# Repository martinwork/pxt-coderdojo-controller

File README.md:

# pxt-coderdojo-controller
This is an open-source, low-cost, do-it-yourself game controller for the micro:bit. You cannot purchase a finished product. Instead, you'll need to gather all the components and assemble it yourself or with your class.  
[Read more in the hardware section for a detailed building guide](https://github.com/jimd80/pxt-coderdojo-controller/tree/main/hardware)

## Features
* 8 buttons: Up, Down, Left, Right, X, Y, A, B
* 2x AAA batteries, On/Off switch, and LED indicator
* Built-in speaker and customizable red LED
* Micro USB cable storage compartment
* Protection against short circuits and incorrect I/O usage
* Compatible with micro:bit v1.x and v2.x
* Over 100 hours of battery life

## Usage
Creating software for this controller can be done with [Microsoft MakeCode for micro:bit](https://makecode.microbit.org/)
* Create a new project and give it a name of your choice
* Click on Extensions in the block menu
* Search for coderDojo-controller and click on the thumbnail

After adding the extension, you'll find the specific blocks for this controller under ``Dojo Controller``

The blocks work the same as the standard micro:bit A and B buttons and can be used in 2 ways:  

* An event driven approach: use the ``on button pressed`` block. The code inside gets executed when a button is pressed/clicked. The behaviour can be changed to execute the code if the button is released instead.

```blocks
coderDojoController.onButtonPress(CoderDojoButtonID.X, CoderDojoButtonEvent.Pressed, function () {
    coderDojoController.setRedLed(CoderDojoLedState.On)
})
```

```blocks
coderDojoController.onButtonPress(CoderDojoButtonID.X, CoderDojoButtonEvent.Released, function () {
    coderDojoController.setRedLed(CoderDojoLedState.Off)
})
```

* Alternatively, a loop driven approach can be used with a standard ``if`` block combined with the ``button is pressed`` function. The code inside the ``if`` block will be executed multiple times, as long as the button is being pressed.

```blocks
basic.forever(function () {
    if (coderDojoController.buttonIsPressed(CoderDojoButton.X, CoderDojoButtonState.Pressed)) {
        coderDojoController.setRedLed(CoderDojoLedState.On)
    } else {
        coderDojoController.setRedLed(CoderDojoLedState.Off)
    }
})
```

Note that the A and B buttons on the micro:bit have the same function as the A and B buttons on the controller. You can use the extension without the controller hardware and have the extra buttons available when plugged into the controller.

## Build
cd into project folder  
npm install pxt  
pxt target microbit  
pxt gendocs --locs  
if needed: update translations in _locales/  
pxt build  

## Supported targets

* for PXT/microbit
(The metadata above is needed for package search.)

## License

MIT  

```package
coderdojo-controller=github:jimd80/pxt-coderdojo-controller
```

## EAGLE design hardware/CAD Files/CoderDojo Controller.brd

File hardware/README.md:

## Hardware building guide
The (empty) PCB can be easily manufactured by any PCB company, for example JLCPCB which is known as the cheapest. The cable holder at the back can be 3D printed with any 3D printer, for example the affordable Creality Ender V2 or V3.

Other parts can be ordered at various electronics suppliers such as LCSC, Aliexpress, Digikey, Farnell, ... The most difficult part to source will be the Micro:bit EDGE Connector. This needs to be the horizontal SMD type. Start finding this connector first before deciding to build this project.

Soldering can be done with (Lead free) soldering paste and a reflow oven, or if you are a bit handy it can also be done with a classical soldering iron, lead-free soldering wire and some flux. In that case it will be handy to have something to keep the parts in place while soldering, such as a screwdriver.

## Tools needed

You'll needs some tools and skills to build this project.
- A soldering iron and lead-free soldering wire
- Optionally, a reflow oven OR a hot air gun. Using this option you'll also need lead-free solder paste, such as Chipquik TS391SNL
- Recommended: Flux, such as Chipquik SMD291NL
- Cutting plier

## Step 1: Ordering the parts
Check out the [Bill of materials](https://github.com/jimd80/pxt-coderdojo-controller/blob/main/hardware/Bom.ods?raw=true). Parts can be ordered at various suppliers.

Part number      |Reference	            |Description                      |Qty|Price|Order link example|
:----------------|:---------------------|:--------------------------------|--:|----:|:-----------------|
R1,2,3,4,8,9     |Res 1K SMD0805        |Resistor 1K / 1% / 0,1W / 0805   |  6|€0.06|[LCSC](https://www.lcsc.com/product-detail/Chip-Resistor-Surface-Mount_YAGEO-RC0805FR-071KL_C95781.html)|
R5               |Res 100R SMD0805      |Resistor 100R / 1% / 0,1W / 0805 |  1|€0.01|[LCSC](https://www.lcsc.com/product-detail/Chip-Resistor-Surface-Mount_YAGEO-RC0805FR-07100RL_C105577.html)|
R6,7             |Res 470R SMD0805      |Resistor 470R / 1% / 0,1W / 0805 |  2|€0.02|[LCSC](https://www.lcsc.com/product-detail/Chip-Resistor-Surface-Mount_YAGEO-RC0805FR-07470RL_C114564.html)|
C1,2 (Optional)  |Cap 4u7 16v SMD1206   |Capacitor 4u7 / 16V / SMD 1206   |  2|€0.04|[LCSC](https://www.lcsc.com/product-detail/Multilayer-Ceramic-Capacitors-MLCC-SMD-SMT_Samsung-Electro-Mechanics-CL31B475KBHNNNE_C51205.html)|
LD1              |LED Red SMD0805       |Led Red SMD 0805                 |  1|€0.02|[LCSC](https://www.lcsc.com/product-detail/LED-Indication-Discrete_XINGLIGHT-XL-2012SURC_C965812.html)|
LD2              |LED Green SMD0805     |Led Green SMD 0805               |  1|€0.02|[LCSC](https://www.lcsc.com/product-detail/LED-Indication-Discrete_XINGLIGHT-XL-2012UGC_C965815.html)|
F1               |Polyfuse 500mA SMD1812|Polyfuse 30V / 500mA / SMD 1812  |  1|€0.08|[Aliexpress](https://www.aliexpress.com/item/1005006431435556.html)|
BUZ1             |9042 16R Passive      |Passive piezo sounder 3-5v       |  1|€0.19|[Aliexpress](https://www.aliexpress.com/item/1005006230919996.html)|
SW1,2,3,4,6,7,8,9|Pushbutton 6x6x5mm    |Pushbutton (on)-off 6x6x5mm      |  8|€0.05|[Aliexpress](https://www.aliexpress.com/item/1005001897291190.html)|
SW5              |Switch SS-12F23       |Slider switch 50v/0,5A spdt      |  1|€0.08|[Aliexpress](https://www.aliexpress.com/item/1005004508647910.html)|
BATT1            |2XAAA Battery Box     |Battery holder 2x AAA center hole|  1|€0.36|[Aliexpress](https://www.aliexpress.com/item/1005006274732583.html)|
J1               |Edge connector hor SMD|Micro:bit edge connector SMD/hor |  1|€0.85|[Aliexpress](https://www.aliexpress.com/item/1005006206948907.html)|
Other            |SMTSO M3 1ET          |SMD M3 Nut Length 1,5 + 1mm      |  1|€0.22|[Aliexpress](https://www.aliexpress.com/item/1005007226371037.html)|
Other            |Screw M3x6            |Screw M3x6 countersunk           |  1|€0.04|[Aliexpress](https://www.aliexpress.com/item/4000983507018.html)|

- C1 and C2 are not really required but can avoid software resets when shaking the controller heavilly
- BUZ1 is not required if using a micro:bit v2 or if sound is not preferred
- The most difficult part to find will be the EDGE connector, this needs to be the horizontal SMD version, and needs to look exactely like this

## Step 2: Ordering the PCB
The PCB (without components) needs to be manufactored by a company. These are the instructions for JLCPCB.
- Go to (https://jlcpcb.com)
- Choose "Add gerber file" and upload [CoderDojo Controller JLCPCB order.zip](https://github.com/jimd80/pxt-coderdojo-controller/blob/main/hardware/CoderDojo%20Controller%20JLCPCB%20order.zip?raw=true)
- Select your desired quantity (the more the cheaper per board)
- Change PCB Color to Black
- Change Surface Finish to LeadFree HASL (If ROHS is required in your country, always the case for the EU)
- Choose Mark on PCB: Remove Mark  
All other options are oke by default. Complete the order process.

## Step 3: 3D Print the cable holder
This step is not required if you don't want to have the cable storage at the back of the controller. In that case, the screw needs to be M3x5 instead of M3x6.
- Download [Cable holder 3D Print.stl](https://github.com/jimd80/pxt-coderdojo-controller/blob/main/hardware/CAD%20Files/Cable%20holder%203D%20Print.stl?raw=true)
- Process the file in your slicer. Recommended layer height is 0.2mm and recommended speed is 50mm/s
- Print it, preferable with black PETG as this is more fire resistant than PLA or ABS

## Step 4: Solder the SMD parts
In the [Bill of materials](https://github.com/jimd80/pxt-coderdojo-controller/blob/main/hardware/Bom.ods?raw=true) you'll find which parts belongs to which part numbers printed on the PCB (such as R1, C1, ...). Only for the 2 LED's the direction of the part (polarity) matters. There is usually an indicator, like a small green dot or a line) that should point in the direction of the arrow on the PCB.
Also solder the special M3 nut in the middle. Avoid putting excess solder at the back side as that surface needs to stay flat for the battery box.

Soldering SMD parts can be done in several ways, there are many tutorials online such as https://www.youtube.com/watch?v=hoLf8gvvXXU or https://www.youtube.com/watch?v=fYInlAmPnGo

## Step 5: Solder the Edge connector
The EDGE connector is preferably soldered with a soldering iron as it is not clear if it can withstand 240 degrees hot air required for lead-free soldering. Use extra flux to create smooth joints. After soldering, remove the flux with isopropyl alcohol.

## Step 6: Solder the through hole parts
Next, solder the switches and the speaker with a soldering iron and soldering wire. Cut off the excess leads and smoothen the sharp edges at the back with a small file or sanding paper (be careful to not damage the pcb)

## Step 7: Mount the battery box and cable holder
Next, put the battery box through the printed cable holder at the back of the pcb, and fix it with a 6mm M3 screw (conical head). Then, solder the 2 leads of the battery box and cut the excess wire. Note that the leads of the battery box require decent heating to attach to the solder, as these leads are not pre-tinned as you would normally expect. On my prototype, I had regular software resets due to a poor contact due to insufficient heating. The soldering joint looked good, but was not really bounded.

## Step 8: Ready to power up
Always make sure to put the power switch to the OFF position when placing or removing the micro:bit.

Enjoy!

## Optional: Print a storage case
STL files are available in the CAD Files folder for printing a storage case from 2 till 7 controllers. The bottom notch will prevent the contoller to fit nicely when the power button is still on (preventing battery drain)

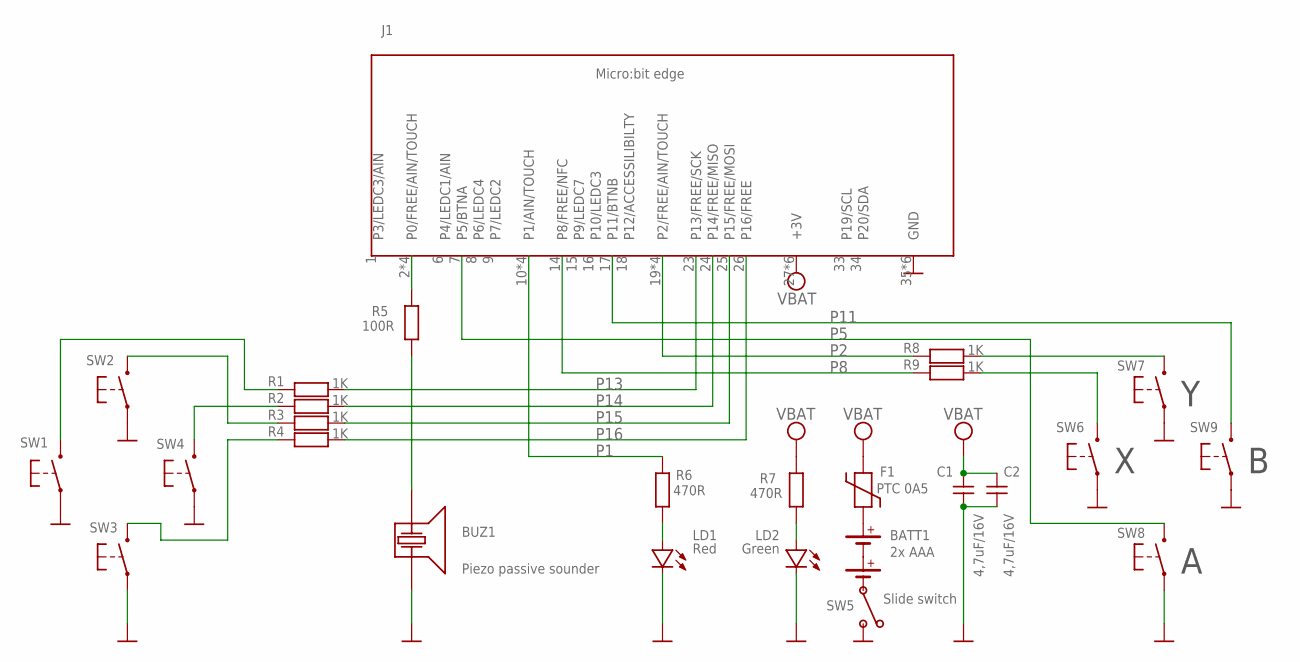
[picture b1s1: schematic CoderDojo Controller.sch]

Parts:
BATT1: CJ2XAAA; SOCKET_2XAAA
BUZ1: CBUZ9; BUZZER9
C1, C2: CC4U7A; CAP_1206
F1: CFPOLY0A5B; RES_1812
J1: CJMBITH; SOCKET_MBIT_H
LD1: CDLEDRDC; LED_0805
LD2: CDLEDGNC; LED_0805
R1, R2, R3, R4, R8, R9: CR1KA; RES_0805
R5: CR100RA; RES_0805
R6, R7: CR470RA; RES_0805
SW1, SW2, SW3, SW4, SW6, SW7, SW8, SW9: CSWPUSHA5; SWITCH_PUSH_5MM
SW5: CSWSS12F23; SWITCH_SS12F23

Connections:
GND: BUZ1.2, C1.1, C2.1, J1.35 (GND), J1.36 (GND), J1.37 (GND), J1.38 (GND), J1.39 (GND), J1.40 (GND), LD1.C, LD2.C, SW1.3, SW1.4, SW2.3, SW2.4, SW3.3, SW3.4, SW4.3, SW4.4, SW5.3 (B), SW6.3, SW6.4, SW7.3, SW7.4, SW8.3, SW8.4, SW9.3, SW9.4
unnamed: R9.2, SW6.1 (S), SW6.2 (S)
unnamed: R8.2, SW7.1 (S), SW7.2 (S)
unnamed: R2.1, SW4.1 (S), SW4.2 (S)
unnamed: R3.1, SW2.1 (S), SW2.2 (S)
unnamed: J1.2 (P0/FREE/AIN/TOUCH), J1.3 (P0/FREE/AIN/TOUCH), J1.4 (P0/FREE/AIN/TOUCH), J1.5 (P0/FREE/AIN/TOUCH), R5.2
unnamed: BUZ1.1, R5.1
unnamed: BATT1.POS (+), F1.1
unnamed: BATT1.NEG (-), SW5.2 (CEN)
unnamed: LD2.A, R7.1
unnamed: LD1.A, R6.1
unnamed: R1.1, SW1.1 (S), SW1.2 (S)
unnamed: R4.1, SW3.1 (S), SW3.2 (S)
P1: J1.10 (P1/AIN/TOUCH), J1.11 (P1/AIN/TOUCH), J1.12 (P1/AIN/TOUCH), J1.13 (P1/AIN/TOUCH), R6.2
P2: J1.19 (P2/FREE/AIN/TOUCH), J1.20 (P2/FREE/AIN/TOUCH), J1.21 (P2/FREE/AIN/TOUCH), J1.22 (P2/FREE/AIN/TOUCH), R8.1
P5: J1.7 (P5/BTNA), SW8.1 (S), SW8.2 (S)
P8: J1.14 (P8/FREE/NFC), R9.1
P11: J1.17 (P11/BTNB), SW9.1 (S), SW9.2 (S)
P13: J1.23 (P13/FREE/SCK), R1.2
P14: J1.24 (P14/FREE/MISO), R2.2
P15: J1.25 (P15/FREE/MOSI), R3.2
P16: J1.26 (P16/FREE), R4.2
VBAT: C1.2, C2.2, F1.2, J1.27 (+3V), J1.28 (+3V), J1.29 (+3V), J1.30 (+3V), J1.31 (+3V), J1.32 (+3V), R7.2

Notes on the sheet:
Piezo passive sounder

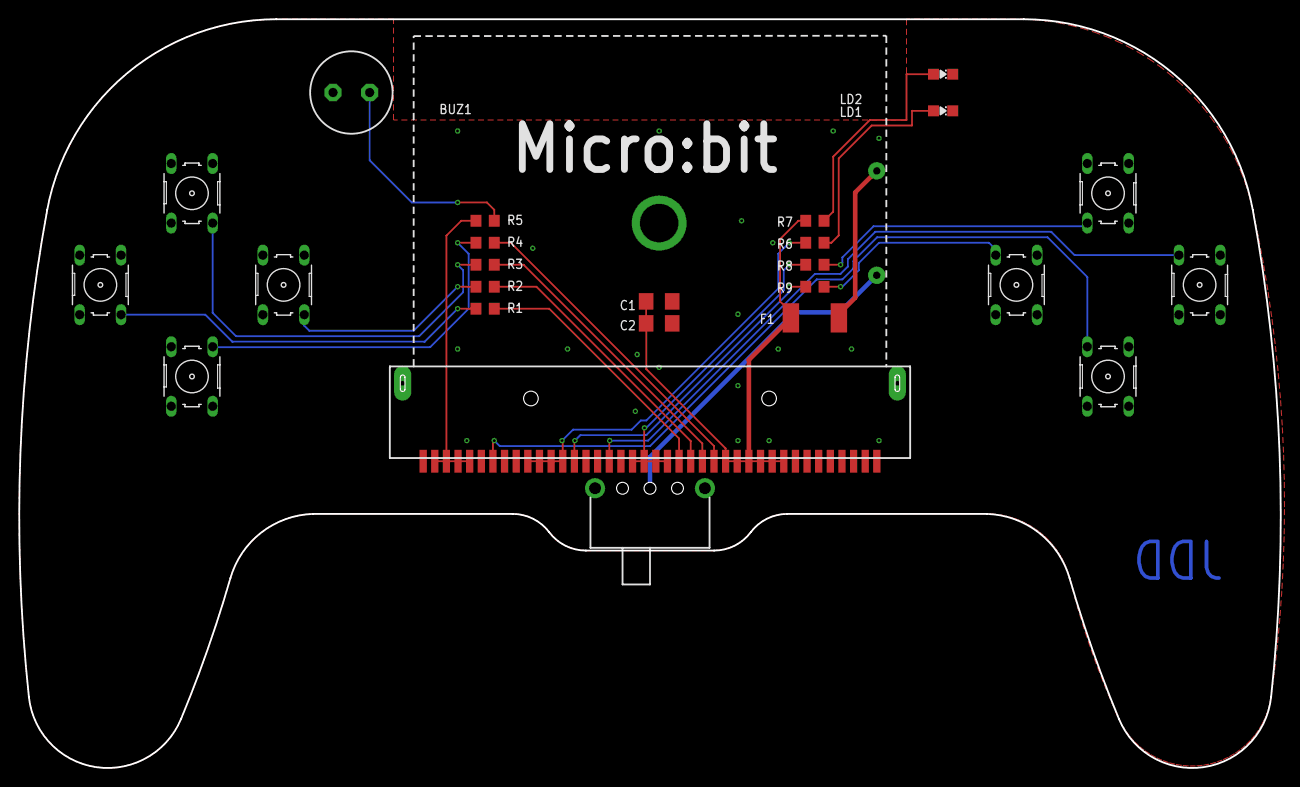
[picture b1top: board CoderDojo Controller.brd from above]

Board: 2 copper layers, 137.7 x 81.7 mm, 26 parts (1 on the bottom side), 23 nets.

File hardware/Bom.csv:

Part(s)	Reference	Description	Supplier	Supplier ref	Quantity	Estimated price	Subtotal
R1, R2, R3, R4, R8, R9	Res 1K SMD0805	1K / 1% / 0,1W / 0805	LCSC	C95781	6	€ 0,01	€ 0,06
R5	Res 100R SMD0805	100R / 1% / 0,1W / 0805	LCSC	C105577	1	€ 0,01	€ 0,01
R6, R7	Res 470R SMD0805	470R / 1% / 0,1W / 0805	LCSC	C114564	2	€ 0,01	€ 0,02
C1, C2 (Optional)	Cap 4u7 16v SMD1206	Capacitor ceramic 4u7 / 16V / SMD 1206	LCSC	C51205	2	€ 0,02	€ 0,04
LD1	LED Red SMD0805	Led Red 625nm / 120 deg / 20mA / 2V / SMD 0805	LCSC	C965812	1	€ 0,02	€ 0,02
LD2	LED Green SMD0805	Led Green 568nm / 120 deg / 20mA / 2,2V / SMD 0805	LCSC	C965815	1	€ 0,02	€ 0,02
F1	Polyfuse 500mA SMD1812	Polyfuse 30V/500mA	Aliexpress	https://www.aliexpress.com/item/1005006431435556.html	1	€ 0,08	€ 0,08
BUZ1	9042 16R Passive	Passive piezo sounder 3-5v	Aliexpress	https://www.aliexpress.com/item/1005006230919996.html	1	€ 0,19	€ 0,19
SW1,2,3,4,6,7,8,9	Pushbutton 6x6x5mm	drukknop (on)-off 6x6mm print height 5mm	Aliexpress	https://www.aliexpress.com/item/1005001897291190.html	8	€ 0,05	€ 0,40
SW5	Switch SS-12F23	50v/0,5A spdt	Aliexpress	https://www.aliexpress.com/item/1005004508647910.html	1	€ 0,08	€ 0,08
BATT1	2XAAA Box	Battery holder 2x AAA with center hole	Aliexpress	https://www.aliexpress.com/item/1005006274732583.html	1	€ 0,36	€ 0,36
J1	Edge connector horizontal SMD	Micro:bit edge connector	Aliexpress	https://www.aliexpress.com/item/1005006206948907.html	1	€ 0,85	€ 0,85
Other 1	SMTSO M3 1ET	SMD M3 Nut Length 1,5 + 1mm	Aliexpress	https://www.aliexpress.com/item/1005007226371037.html	1	€ 0,22	€ 0,22
Other 2	Screw M3x6	Screw M3x6 countersunk	Aliexpress	https://www.aliexpress.com/item/4000983507018.html	1	€ 0,04	€ 0,04
Other 3	Cable holder	3D Printed Cable Holder PETG Black		Cable holder 3D Print.stl	1	€ 0,50	€ 0,50
Other 4	PCB	CoderDojo Controller circuit board	JLCPCB	CoderDojo Controller JLCPCB order.zip	1	€ 1,00	€ 1,00
Total							€ 3,89

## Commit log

2025-04-18 First development
2025-04-18 Rename labels
2025-04-18 update]
2025-04-19 Added hardware files
2025-04-19 corrected csv
2025-04-19 undo tsv
2025-04-19 Changed icon
2025-04-19 fix ratio
2025-04-20 refactoring
2025-04-20 bugfix
2025-04-20 fixes
2025-04-20 Initial fixes
2025-04-20 Use arrow icons instead of text
2025-04-20 locales fix
2025-04-20 Replaces text by icons
2025-04-20 apply guidelines for approval
2025-04-20 Fix broken link
2025-04-21 Added building guide
2025-04-21 Added bom and images in doc
2025-04-21 Small corrections
2025-04-25 align to requirements for extension approval
2025-04-25 typo fix
2025-04-25 minor fixes and added gitignore
2025-04-25 Fix makecode simulator crash
2025-04-25 fix french display bug, translation cannot start with % ?
2025-04-25 translation fix
2025-04-26 fix typos
2025-05-02 Minor fixes for makecode approval
2025-05-03 Aligned with guidelines
2025-05-04 Completed documentation
2025-05-04 Documentation fix
2025-05-04 type in dutch translation
2025-05-04 Minor documentation fixes
2025-05-04 fix example
